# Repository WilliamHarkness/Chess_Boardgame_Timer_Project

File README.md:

# Chess Clock

This repository contains a simple Chess Clock application implemented in Arduino IDE language (C? / C++?)

## Features

- Poker mode including hand counter, timer and individual player timer.
- Up counting mode. 1-9 players (for other timing purposes). 
- Down counting mode. 1-9 players (for other timing purposes). Includes time back, and individual time custimization
- Buzzer 
- Loop mode 1-9 players. Loops timer. Good for turn timer. Resets to default on button press
-Battery opperated

## Blender file for 3d printing

- This file is what was used for the 3d printing

## KiCAN file for PCB

- Main board and Display board for each display
- Used jlbPCB for printing. Was pretty useful. 

## Partlist 

## Partlist 

| Component              | Part Number/Description                                                                                                 |
|------------------------|--------------------------------------------------------------------------------------------------------------------------|
| ATMEGA                 | ATMEGA32                                                                                                                 |
| Control SW             | SW-PB1-1DZ-A-P1-A                                                                                                       |
| Multiplexer            | CD4028BM96                                                                                                               |
| Buzzer                 | WST-1210T                                                                                                                |
| Battery Holder         | 36-234-ND                                                                                                                |
| 5v Switching Reg       | AP63205QWU-7                                                                                                             |
| Inductor               | B78108E1472K000                                                                                                          |
| Caps 100nF 0603       |                                                                                                                          |
| Caps 22uF 0603        |                                                                                                                          |
| Main Button (Amazon)   | DaierTek 6pcs 12V Momentary Push Button Switch 12mm Waterproof Small Round Mini Micro Black Metal Power Pushbutton SPST for Car RV Marine Boat Automotive   |
| Power Button (Amazon)  | QTEATAK 5Pcs On/Off Boat Rocker Switch 5Pcs 2 Pin 2 Position Snap 12V 110V 250V                                        |
| Player Button          | 12Pcs Arcade Joystick Game Console Buttons 30mm Replacement Button for Most Hori and for MadCatz, Snap in Installation |

## ETC

I may be missing some parts from the list. I got most on digikey and the rest on amazon.
This design should be simplified But was sucessful for my purposes.

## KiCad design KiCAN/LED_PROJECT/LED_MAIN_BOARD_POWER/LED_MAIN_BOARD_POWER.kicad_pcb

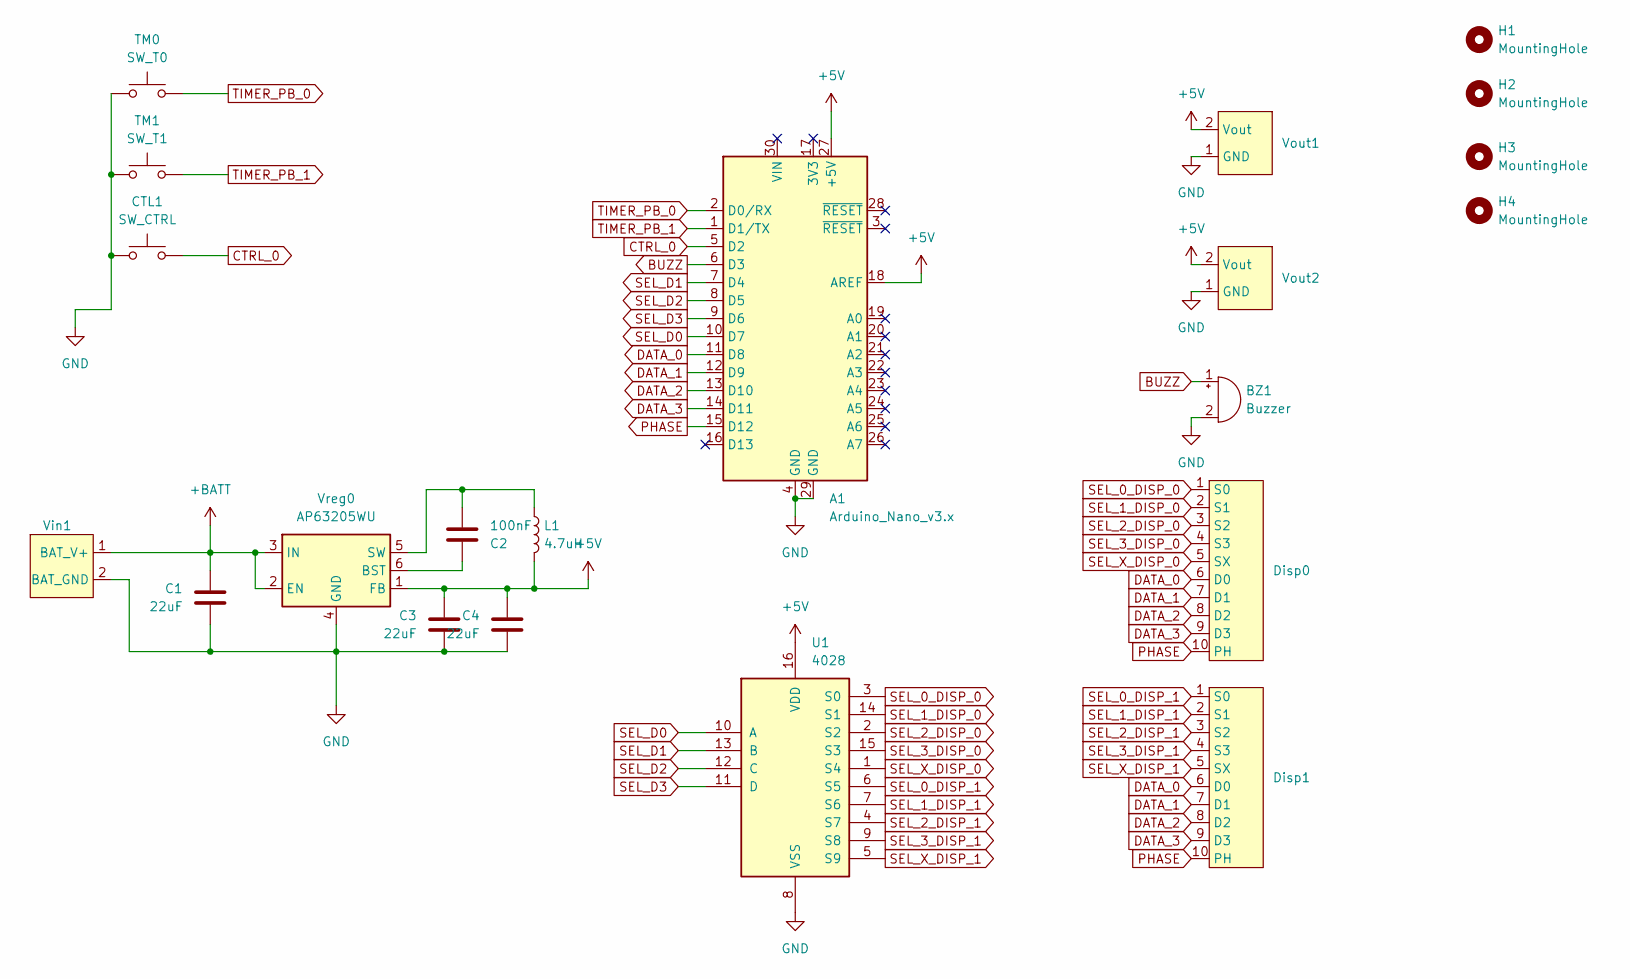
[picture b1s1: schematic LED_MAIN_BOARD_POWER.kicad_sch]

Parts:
A1: Arduino_Nano_v3.x; Arduino_Nano
BZ1: Buzzer; Buzzer_12x9.5RM7.6
C1, C3, C4: 22uF; C_0603_1608Metric_Pad1.08x0.95mm_HandSolder
C2: 100nF; C_0603_1608Metric_Pad1.08x0.95mm_HandSolder
CTL1: SW_CTRL; 2-Pad_FP
Disp0, Disp1: 10-Pad-OP
H1, H2, H3, H4: MountingHole; MountingHole_3.2mm_M3
L1: 4.7uH; R_Axial_DIN0207_L6.3mm_D2.5mm_P10.16mm_Horizontal
TM0: SW_T0; 2-Pad_FP
TM1: SW_T1; 2-Pad_FP
U1: 4028; SOIC-16_3.9x9.9mm_P1.27mm
Vin1: 2-Pad_FP
Vout1, Vout2: 2-Pad_FP
Vreg0: AP63205WU; TSOT-23-6_HandSoldering

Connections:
+5V: A1.18 (AREF), A1.27 (+5V), C3.1, C4.1, L1.2, U1.16 (VDD), Vout1.2 (Vout), Vout2.2 (Vout), Vreg0.1 (FB)
+BATT: C1.1, Vin1.1 (BAT_V+), Vreg0.2 (EN), Vreg0.3 (IN)
BUZZ: A1.6 (D3), BZ1.1 (-)
CTRL_0: A1.5 (D2), CTL1.2
DATA_0: A1.11 (D8), Disp0.6 (D0), Disp1.6 (D0)
DATA_1: A1.12 (D9), Disp0.7 (D1), Disp1.7 (D1)
DATA_2: A1.13 (D10), Disp0.8 (D2), Disp1.8 (D2)
DATA_3: A1.14 (D11), Disp0.9 (D3), Disp1.9 (D3)
GND: A1.4 (GND), A1.29 (GND), BZ1.2 (+), C1.2, C3.2, C4.2, CTL1.1, TM0.1, TM1.1, U1.8 (VSS), Vin1.2 (BAT_GND), Vout1.1 (GND), Vout2.1 (GND), Vreg0.4 (GND)
unnamed: C2.1, Vreg0.6 (BST)
unnamed: C2.2, L1.1, Vreg0.5 (SW)
PHASE: A1.15 (D12), Disp0.10 (PH), Disp1.10 (PH)
SEL_0_DISP_0: Disp0.1 (S0), U1.3 (S0)
SEL_0_DISP_1: Disp1.1 (S0), U1.6 (S5)
SEL_1_DISP_0: Disp0.2 (S1), U1.14 (S1)
SEL_1_DISP_1: Disp1.2 (S1), U1.7 (S6)
SEL_2_DISP_0: Disp0.3 (S2), U1.2 (S2)
SEL_2_DISP_1: Disp1.3 (S2), U1.4 (S7)
SEL_3_DISP_0: Disp0.4 (S3), U1.15 (S3)
SEL_3_DISP_1: Disp1.4 (S3), U1.9 (S8)
SEL_D0: A1.10 (D7), U1.10 (A)
SEL_D1: A1.7 (D4), U1.13 (B)
SEL_D2: A1.8 (D5), U1.12 (C)
SEL_D3: A1.9 (D6), U1.11 (D)
SEL_X_DISP_0: Disp0.5 (SX), U1.1 (S4)
SEL_X_DISP_1: Disp1.5 (SX), U1.5 (S9)
TIMER_PB_0: A1.2 (D0/RX), TM0.2
TIMER_PB_1: A1.1 (D1/TX), TM1.2

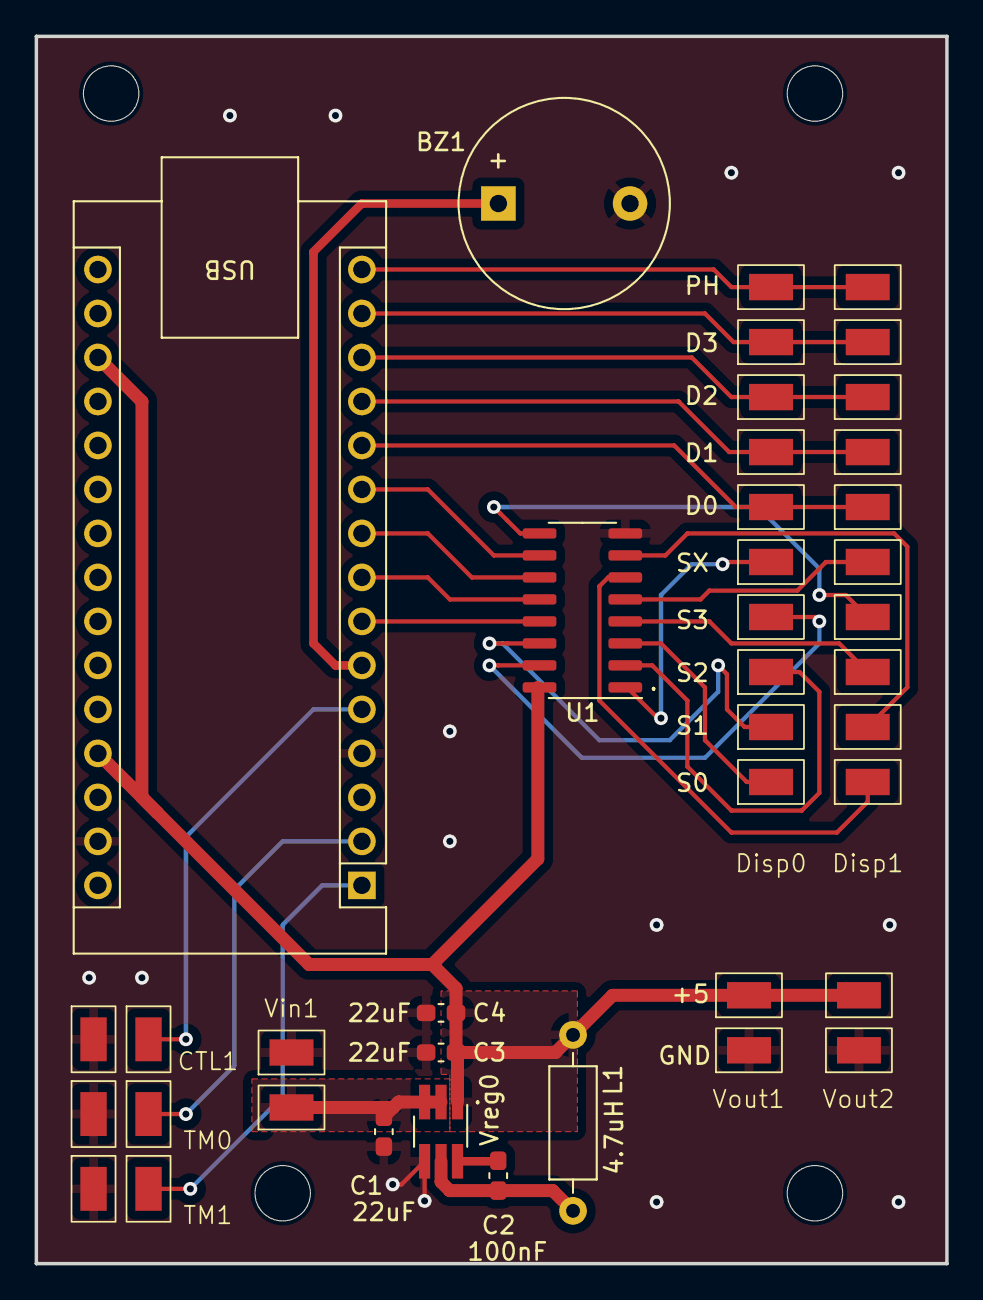
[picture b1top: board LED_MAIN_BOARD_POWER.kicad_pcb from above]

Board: 2 copper layers, 52.6 x 70.9 mm, 21 parts (0 on the bottom side), 28 nets.

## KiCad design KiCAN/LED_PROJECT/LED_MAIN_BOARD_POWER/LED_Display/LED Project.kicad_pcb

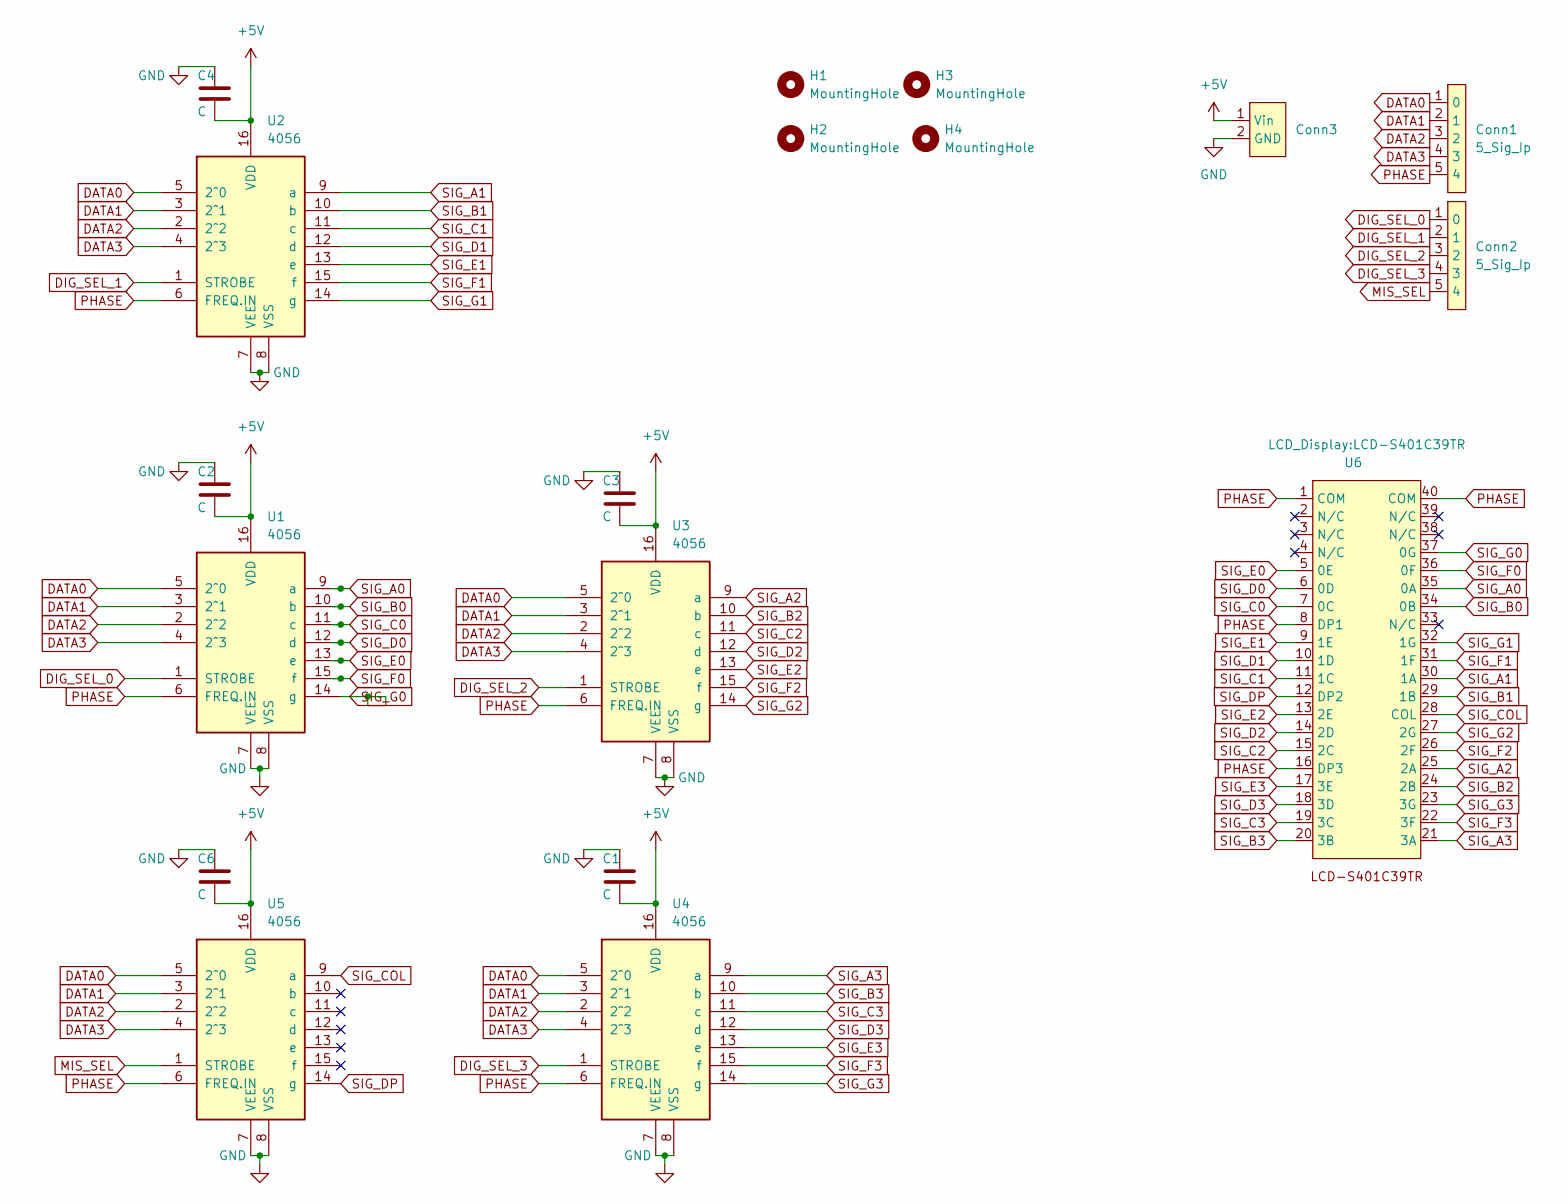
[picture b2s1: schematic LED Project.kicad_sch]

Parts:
C1, C2, C3, C4, C6: C; C_0603_1608Metric
Conn1, Conn2: 5_Sig_Ip; PAD_5
Conn3: PAD_2
H1, H2, H3, H4: MountingHole; MountingHole_2.2mm_M2
U1, U2, U3, U4, U5: 4056; SOIC-16_3.9x9.9mm_P1.27mm
U6: LCD-S401C39TR

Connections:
+5V: C1.2, C2.2, C3.2, C4.2, C6.2, Conn3.1 (Vin), U1.16 (VDD), U2.16 (VDD), U3.16 (VDD), U4.16 (VDD), U5.16 (VDD)
DATA0: Conn1.1 (0), U1.5 (2^0), U2.5 (2^0), U3.5 (2^0), U4.5 (2^0), U5.5 (2^0)
DATA1: Conn1.2 (1), U1.3 (2^1), U2.3 (2^1), U3.3 (2^1), U4.3 (2^1), U5.3 (2^1)
DATA2: Conn1.3 (2), U1.2 (2^2), U2.2 (2^2), U3.2 (2^2), U4.2 (2^2), U5.2 (2^2)
DATA3: Conn1.4 (3), U1.4 (2^3), U2.4 (2^3), U3.4 (2^3), U4.4 (2^3), U5.4 (2^3)
DIG_SEL_0: Conn2.1 (0), U1.1 (STROBE)
DIG_SEL_1: Conn2.2 (1), U2.1 (STROBE)
DIG_SEL_2: Conn2.3 (2), U3.1 (STROBE)
DIG_SEL_3: Conn2.4 (3), U4.1 (STROBE)
GND: C1.1, C2.1, C3.1, C4.1, C6.1, Conn3.2 (GND), U1.7 (VEE), U1.8 (VSS), U2.7 (VEE), U2.8 (VSS), U3.7 (VEE), U3.8 (VSS), U4.7 (VEE), U4.8 (VSS), U5.7 (VEE), U5.8 (VSS)
MIS_SEL: Conn2.5 (4), U5.1 (STROBE)
PHASE: Conn1.5 (4), U1.6 (FREQ.IN), U2.6 (FREQ.IN), U3.6 (FREQ.IN), U4.6 (FREQ.IN), U5.6 (FREQ.IN), U6.1 (COM), U6.8 (DP1), U6.16 (DP3), U6.40 (COM)
SIG_A0: U1.9 (a), U6.35 (0A)
SIG_A1: U2.9 (a), U6.30 (1A)
SIG_A2: U3.9 (a), U6.25 (2A)
SIG_A3: U4.9 (a), U6.21 (3A)
SIG_B0: U1.10 (b), U6.34 (0B)
SIG_B1: U2.10 (b), U6.29 (1B)
SIG_B2: U3.10 (b), U6.24 (2B)
SIG_B3: U4.10 (b), U6.20 (3B)
SIG_C0: U1.11 (c), U6.7 (0C)
SIG_C1: U2.11 (c), U6.11 (1C)
SIG_C2: U3.11 (c), U6.15 (2C)
SIG_C3: U4.11 (c), U6.19 (3C)
SIG_COL: U5.9 (a), U6.28 (COL)
SIG_D0: U1.12 (d), U6.6 (0D)
SIG_D1: U2.12 (d), U6.10 (1D)
SIG_D2: U3.12 (d), U6.14 (2D)
SIG_D3: U4.12 (d), U6.18 (3D)
SIG_DP: U5.14 (g), U6.12 (DP2)
SIG_E0: U1.13 (e), U6.5 (0E)
SIG_E1: U2.13 (e), U6.9 (1E)
SIG_E2: U3.13 (e), U6.13 (2E)
SIG_E3: U4.13 (e), U6.17 (3E)
SIG_F0: U1.15 (f), U6.36 (0F)
SIG_F1: U2.15 (f), U6.31 (1F)
SIG_F2: U3.15 (f), U6.26 (2F)
SIG_F3: U4.15 (f), U6.22 (3F)
SIG_G0: U1.14 (g), U6.37 (0G)
SIG_G1: U2.14 (g), U6.32 (1G)
SIG_G2: U3.14 (g), U6.27 (2G)
SIG_G3: U4.14 (g), U6.23 (3G)

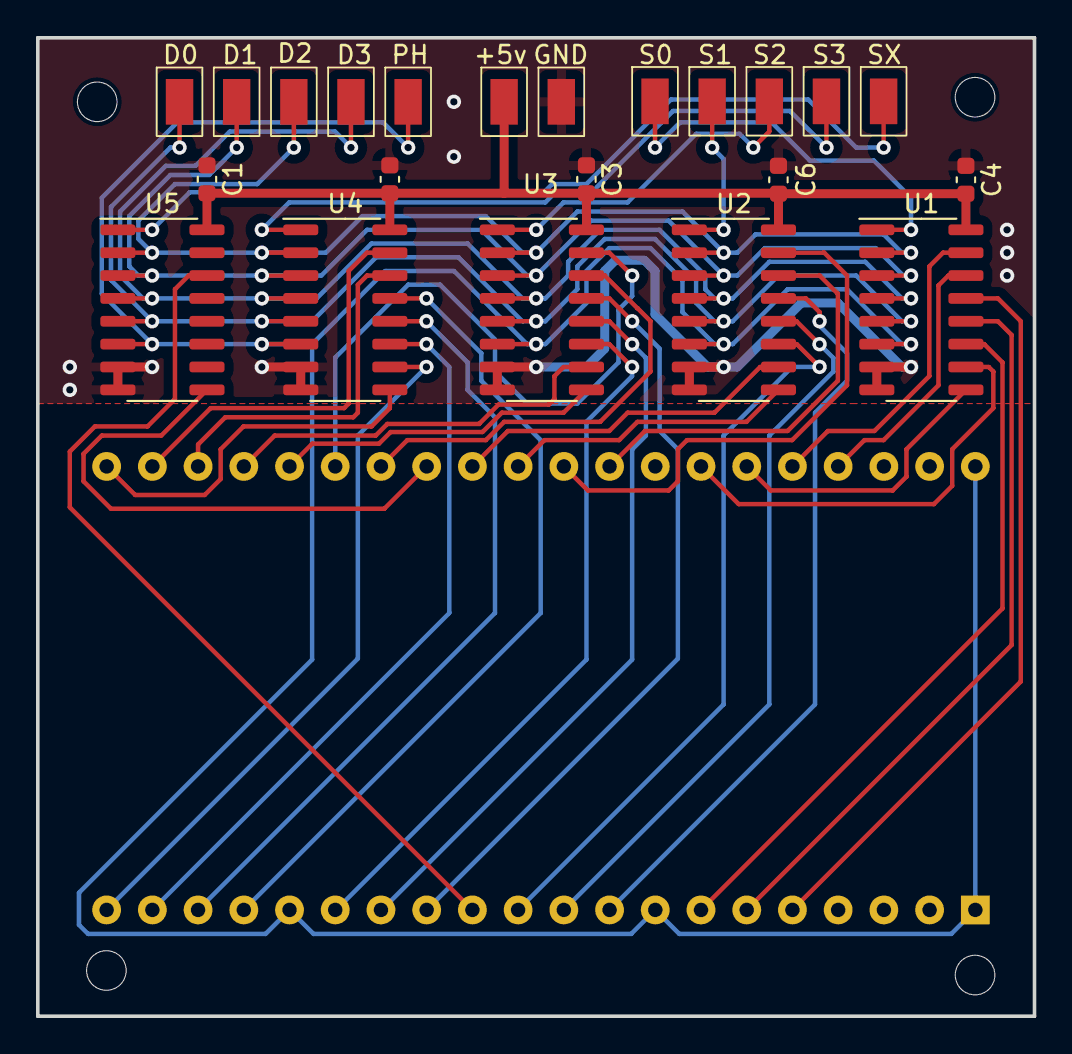
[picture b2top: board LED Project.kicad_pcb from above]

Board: 2 copper layers, 55.4 x 54.4 mm, 18 parts (1 on the bottom side), 42 nets.

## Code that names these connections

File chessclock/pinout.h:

#ifndef __PINNOUT_H__
#define __PINNOUT_H__

#define TIMER0_PIN 0U
#define TIMER1_PIN 1U
#define CTRL_PIN 2U

#define BUZZER_PIN 3U

#define SEL0_PIN 7U
#define SEL1_PIN 4U
#define SEL2_PIN 5U
#define SEL3_PIN 6U

#define DATA0_PIN 8U
#define DATA1_PIN 9U
#define DATA2_PIN 10U
#define DATA3_PIN 11U

#define PHASE_PIN 12U

#endif /* __PINNOUT_H__ */

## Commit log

2024-01-08 Init commit
2024-01-08 Better timer interface
2024-01-08 Upcount 2 people working
2024-01-17 Up count N players
2024-02-03 Verson 1.0.0
    Updated clock will complete features
    Probably some bugs still.
    Not "clean" but done quickly and functional
2024-03-02 Updated.
    Added final changes,
    Added Blender Files
    Added KiCAD filesX
2024-03-02 Moved Files
